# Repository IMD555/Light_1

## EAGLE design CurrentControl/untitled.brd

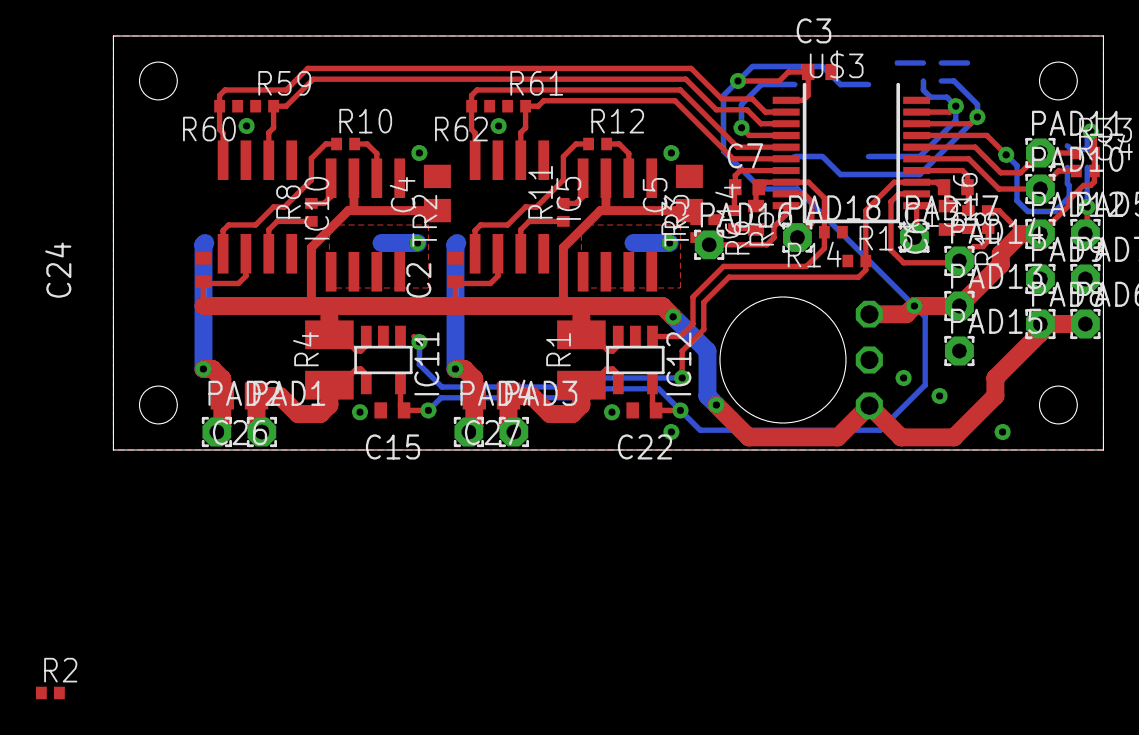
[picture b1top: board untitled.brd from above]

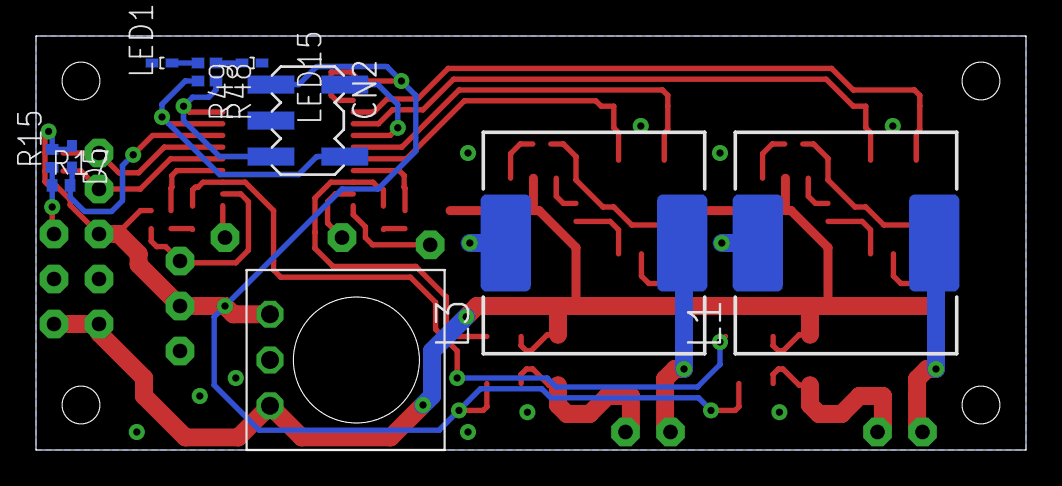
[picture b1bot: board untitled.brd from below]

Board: 2 copper layers, 55.0 x 23.0 mm, 72 parts (11 on the bottom side), 41 nets.

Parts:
C2, C3, C22, C24: 0.1u; C0402
C4, C5, C26, C27: C0805
C6, C7, C13, C14, C15: C0402
CN2: ICSP; MINI-ICSP
D5: VMN2
IC5, IC10: MCP14E5; SO-08
IC11, IC12: INA138; SOT23-5
L1, L3: 22u; SCRH125
LED15: Red; CHIP-LED1005
LED16: Green; CHIP-LED1005
PAD1, PAD2, PAD3, PAD4, PAD5, PAD6, PAD7, PAD8, PAD9, PAD10, PAD11, PAD12, PAD13, PAD14, PAD15, PAD16, PAD17, PAD18: 1,6/0,8
R1, R4: 5m; R1210
R2, R13: 100k; R0402
R3: 33k; R0402
R5, R8, R10, R18: R0402
R6: 3.3k; R0402
R11, R12: 33; R0402
R14: 200k; R0402
R15, R59, R60, R61, R62: 10k; R0402
R16, R33, R34: 15k; R0402
R17: 1k; R0402
R48, R49: 330; R0402
TR2, TR3: MOSFET_N_P_AO4630; SO-08
U$1, U$4, U$5: RULER-S
U$2: 78-DC/DCV; VXO78-500
U$3: PIC16F1769SS; SSOP20

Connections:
GND: C2.2, C3.2, C4.2, C5.2, C15.2, C22.2, C24.2, CN2.GND, IC5.3, IC10.3, IC11.2, IC12.2, LED15.C, LED16.C, PAD7.1, PAD9.1, PAD15.1, R6.1, R13.1, R14.1, R59.1, R60.1, R61.1, R62.1, TR2.1, TR3.1, U$2.2, U$3.20
unnamed: IC11.1, R2.1
unnamed: CN2.VPP, U$3.4
unnamed: PAD16.1, R3.1, R6.2, U$3.10
unnamed: IC5.4, R62.2, U$3.5
unnamed: C26.1, IC11.4, PAD1.1, R4.1
unnamed: IC10.2, R59.2, U$3.3
unnamed: C26.2, L1.2, PAD2.1
unnamed: IC10.4, R60.2, U$3.2
unnamed: CN2.PGD, R48.2, U$3.19
unnamed: IC5.2, R61.2, U$3.6
unnamed: CN2.PGC, R49.2, U$3.18
unnamed: C6.2, C13.2, R2.2, R13.2, U$3.13
unnamed: C7.2, C14.2, IC12.1, R14.2, U$3.8
unnamed: PAD17.1, U$3.11
unnamed: PAD18.1, U$3.9
unnamed: PAD14.1, R16.1, U$3.12
unnamed: C14.1, R5.2
unnamed: L3.1, TR3.5, TR3.6, TR3.7, TR3.8
unnamed: D5.A, R17.2, U$3.17
unnamed: R10.2, TR2.2
unnamed: C27.2, L3.2, PAD4.1
unnamed: C13.1, R18.1, U$3.14
unnamed: L1.1, TR2.5, TR2.6, TR2.7, TR2.8
unnamed: R11.2, TR3.4
unnamed: R12.2, TR3.2
unnamed: R8.2, TR2.4
unnamed: PAD5.1, R15.1, R17.1
unnamed: PAD10.1, R34.1, U$3.15
unnamed: PAD11.1, R33.1, U$3.16
unnamed: IC10.7, R8.1
unnamed: C27.1, IC12.4, PAD3.1, R1.1
unnamed: IC5.7, R11.1
unnamed: C6.1, R18.2
unnamed: C7.1, R5.1, U$3.7
unnamed: LED15.A, R48.1
unnamed: LED16.A, R49.1
unnamed: IC10.5, R10.1
unnamed: IC5.5, R12.1
V+: C2.1, C4.1, C5.1, C24.1, IC5.6, IC10.6, IC11.3, IC12.3, PAD6.1, PAD8.1, R1.2, R3.2, R4.2, TR2.3, TR3.3, U$2.1
VDD: C3.1, C15.1, C22.1, CN2.VCC, D5.C, IC11.5, IC12.5, PAD12.1, PAD13.1, R15.2, R16.2, R33.2, R34.2, U$2.3, U$3.1

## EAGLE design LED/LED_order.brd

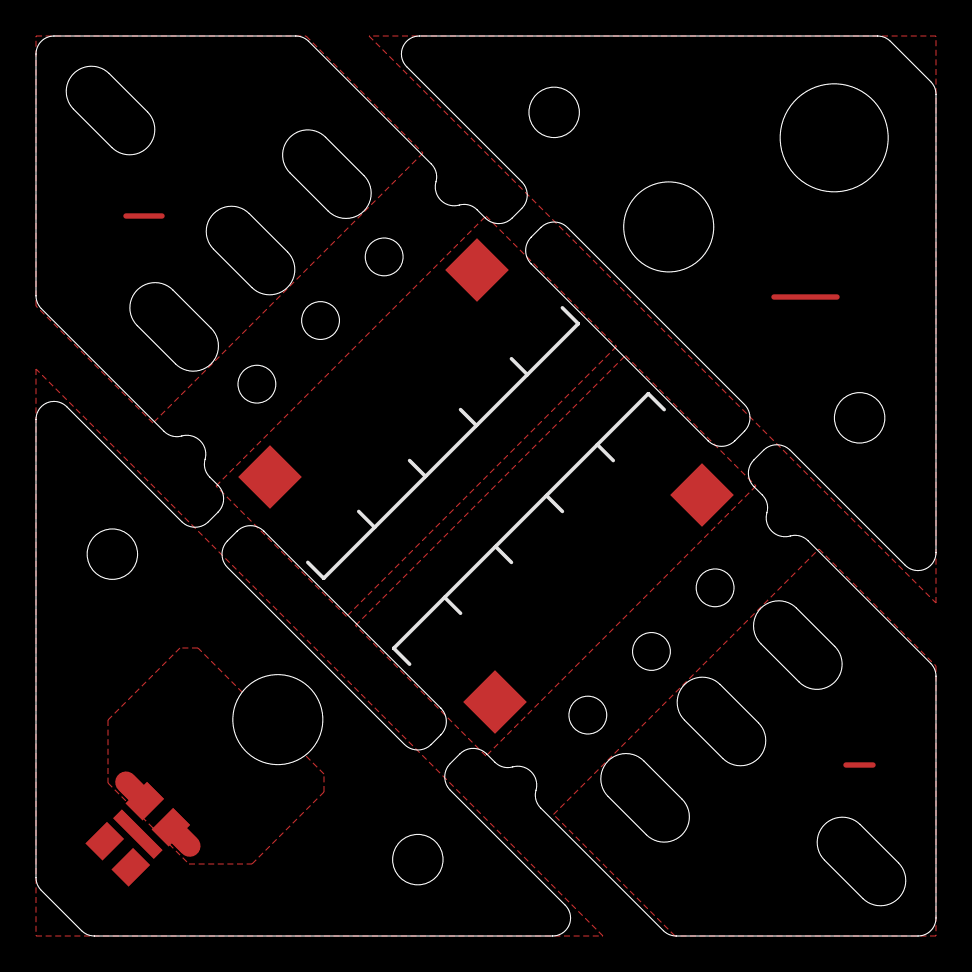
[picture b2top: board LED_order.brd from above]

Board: 2 copper layers, 50.0 x 50.0 mm, 5 parts (0 on the bottom side), 4 nets.

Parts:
LED4: LED_EPML-E; ML-E
PAD1, PAD2, PAD3, PAD4: PAD2.5-2.5; SMD2,5-2,5

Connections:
A: PAD1.1, PAD3.1
A1: LED4.A@1, LED4.A@2
K: PAD2.1, PAD4.1
K1: LED4.C@1, LED4.C@2
